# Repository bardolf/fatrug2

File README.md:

# FATRUG2

Fully automatic time project ([FAT](https://en.wikipedia.org/wiki/Fully_automatic_time)), based on [FireBeetle 2 ESP32-E IoT Microcontroller](https://www.dfrobot.com/product-2195.html). 

Usage demonstrated on [the videos](https://youtube.com/playlist?list=PLJGLIG7klYTQjR2PzYD64GDgjGLkynPeX).

Measures time between starting and finishing device. 
Basic features:
- ESP32-E IoT Microcontroller is a device brain.
- Ultrasonic distance sensor HC-SR04 with a threshold 60 - 80cm, could be more, didn't test.
- Reliable distance between devices up to 100m (depends on local conditions).
- Minimum measurement time is 100ms (avoiding false start).
- Systematic error 20-50ms, which I'm lazy to compansate.
- Able to run several hours on 2500mAh battery.
- Mountable to tripod via 1/4-20 UNC thread.

## Electronics

Schema and PCB drawn in KiCAD and files are part of the project. Original idea (and PCB) relied on laser sensor VL53L0X, however the measurement is too bad in noisy environment (sunny day). It was redesign to use ultrasonic sensor HC-SR04 instead. The ultrasonic sensor needs and TM1637 4-Digit LED need 5V (better results with 5V), step up to 5V was added. It is not yet reflected on PCB (maybe future updates), just connected with dupont wires.

Peripherials are following. 
- MCU

- ~~laser distance sensor - GY-VL53L0X I2, connected via connector labeled _laser_ (SDA, SCL, 3.3V, GND)~~

TODO: ultrasonic sensor

- TM1637 4-Digit LED 0.56" 0.56inch 7 Segments Display, connected via connector labeled _7seg_. Beware: more common display is the one with colon wired and dots unwired. Choose based on your preferences.

- RGB LED NeoPixel WS2812 8mm, connected via connector labeled _RGB LED_

- button (reset), connected to ground and PIN D2 (25) 

- LiPol Batterry 104050 2500mAh 3.7V JST-PH 2.0

- switch ([aliexpress](https://www.aliexpress.com/item/1005003268288232.html?spm=a2g0o.order_detail.0.0.5ad3f19ccqQfnJ))

- 2x resistor 20k - for battery capacity measurement on PIN A0 (36)

- some JST-PH connectors, DUPONT connectors

If you make your own BOM don't forget to [multiply it by two](https://youtube.com/clip/UgkxrPXdP5GEu_9O2kQU0yOqQVvTavGrz9Ro) - you need 2 boxes.

TODO: antennas

### PCB

## Box

## State Diagram 

## Photos

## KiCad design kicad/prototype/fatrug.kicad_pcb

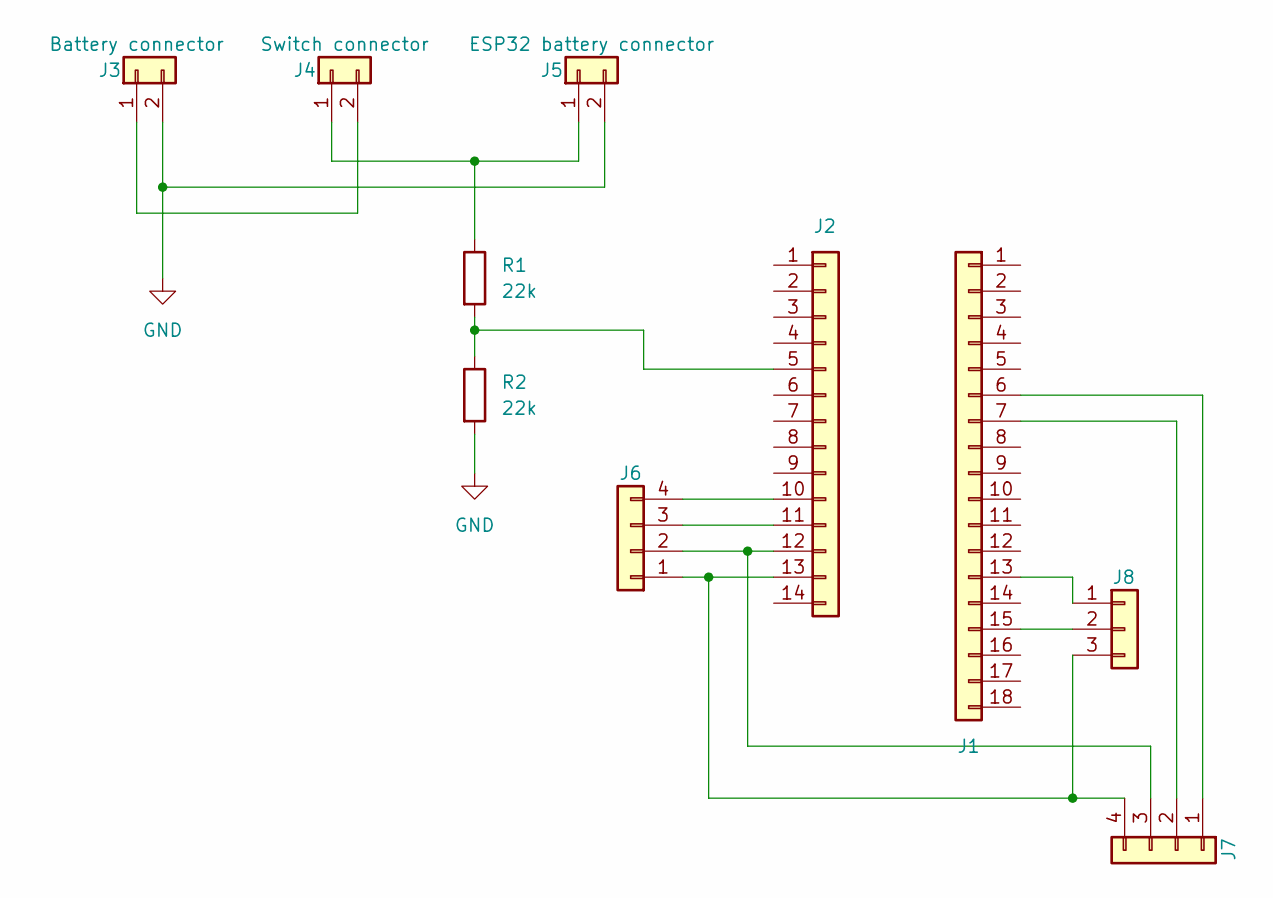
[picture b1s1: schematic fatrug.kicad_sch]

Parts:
J1: Conn_01x18; PinSocket_1x18_P2.54mm_Vertical
J2: Conn_01x14; PinSocket_1x14_P2.54mm_Vertical
J3, J4, J5: Conn_01x02; JST_XH_B2B-XH-AM_1x02_P2.50mm_Vertical
J6, J7: Conn_01x04; PinHeader_1x04_P2.54mm_Vertical
J8: Conn_01x03; PinHeader_1x03_P2.54mm_Vertical
R1, R2: 22k; R_Axial_DIN0204_L3.6mm_D1.6mm_P7.62mm_Horizontal

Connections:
GND: J3.2, J5.2, R2.2
unnamed: J1.6, J7.1
unnamed: J1.7, J7.2
unnamed: J1.13, J8.1
unnamed: J1.15, J8.2
unnamed: J2.10, J6.4
unnamed: J2.11, J6.3
unnamed: J2.12, J6.2, J7.3
unnamed: J2.13, J6.1, J7.4, J8.3
unnamed: J3.1, J4.2
unnamed: J4.1, J5.1, R1.1
unnamed: J2.5, R1.2, R2.1

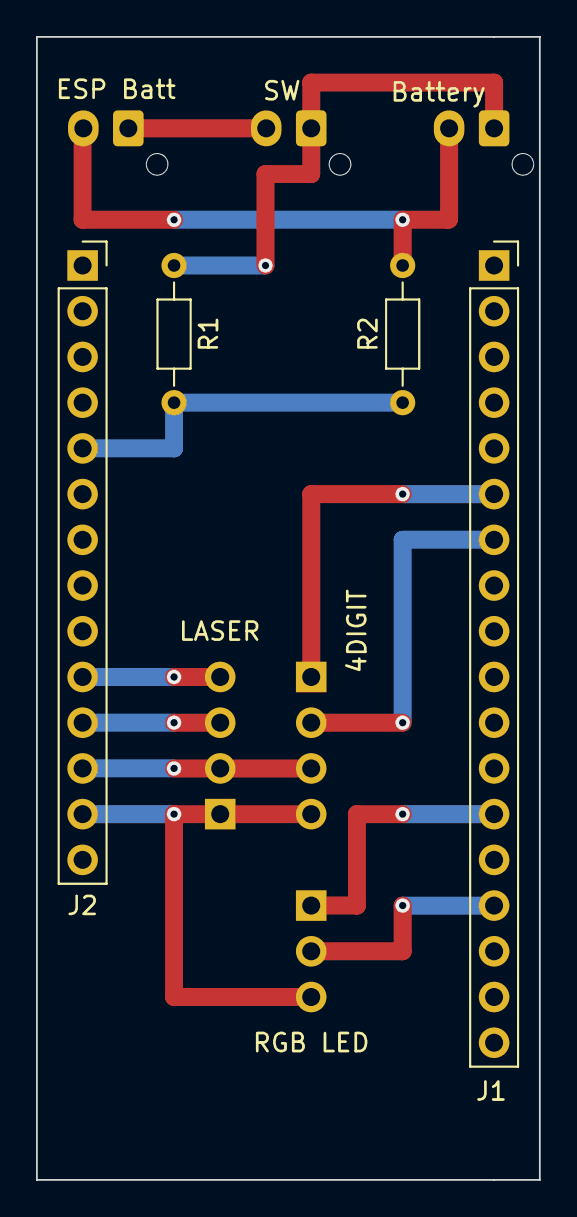
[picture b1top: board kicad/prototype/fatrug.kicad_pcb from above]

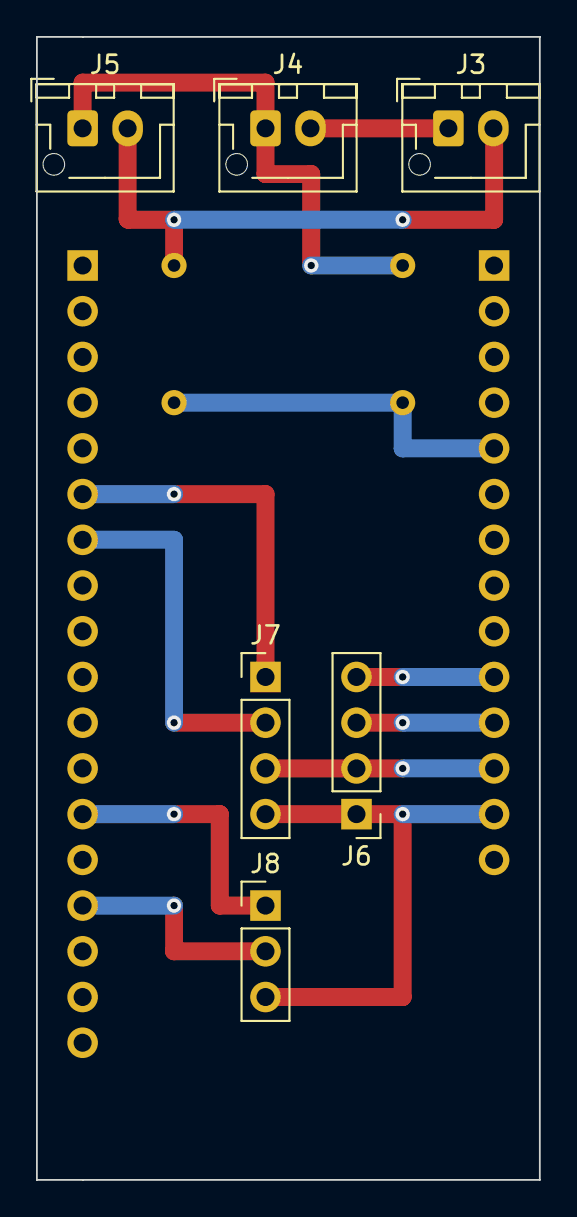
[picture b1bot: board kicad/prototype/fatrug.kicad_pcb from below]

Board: 2 copper layers, 27.9 x 63.5 mm, 10 parts (6 on the bottom side), 12 nets.

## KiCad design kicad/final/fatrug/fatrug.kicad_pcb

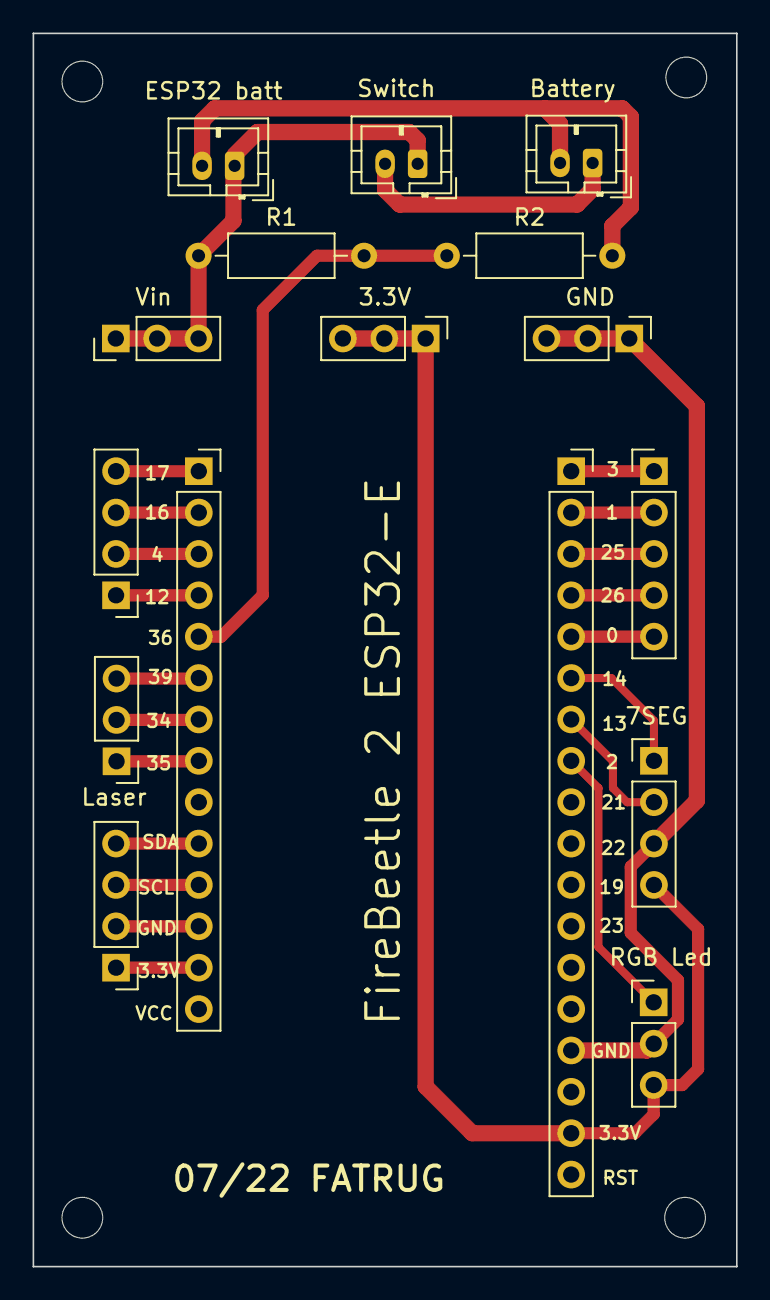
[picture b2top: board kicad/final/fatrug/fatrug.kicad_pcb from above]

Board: 2 copper layers, 43.2 x 75.7 mm, 20 parts (0 on the bottom side), 25 nets.

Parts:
H1, H2, H3, H4: MountingHole; MountingHole_2.5mm
J1, J2, J3: Conn_01x02; JST_PH_B2B-PH-K_1x02_P2.00mm_Vertical
J4, J8, J9: Conn_01x04; PinHeader_1x04_P2.54mm_Vertical
J5: Conn_01x14; PinSocket_1x14_P2.54mm_Vertical
J6: Conn_01x18; PinSocket_1x18_P2.54mm_Vertical
J7, J10, J12, J13, J14: Conn_01x03; PinHeader_1x03_P2.54mm_Vertical
J11: Conn_01x05; PinHeader_1x05_P2.54mm_Vertical
R1, R2: 22k; R_Axial_DIN0207_L6.3mm_D2.5mm_P10.16mm_Horizontal

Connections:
GND: J1.2, J3.2, R2.2
unnamed: J1.1, J2.2
unnamed: J4.1, J5.13
unnamed: J4.2, J5.12
unnamed: J4.3, J5.11
unnamed: J4.4, J5.10
unnamed: J5.1, J9.4
unnamed: J5.2, J9.3
unnamed: J5.3, J9.2
unnamed: J5.4, J9.1
unnamed: J5.5, R1.2, R2.1
unnamed: J5.6, J14.3
unnamed: J5.7, J14.2
unnamed: J5.8, J14.1
unnamed: J6.6, J8.1
unnamed: J6.7, J8.2
unnamed: J6.8, J7.1
unnamed: J6.17, J7.3, J8.4, J13.1, J13.2, J13.3
unnamed: J2.1, J3.1, J10.1, J10.2, J10.3, R1.1
unnamed: J6.1, J11.1
unnamed: J6.2, J11.2
unnamed: J6.3, J11.3
unnamed: J6.4, J11.4
unnamed: J6.5, J11.5
unnamed: J6.15, J7.2, J8.3, J12.1, J12.2, J12.3

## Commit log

2022-08-07 kicad files
2022-08-11 doc updated
2022-08-11 implementation
2022-08-14 freecad box added
2022-08-14 freecad box
2022-08-21 rgbled introduced
2022-08-21 display introduced
2022-08-21 battery introduced
2022-08-23 comment on battery capacity
2022-08-25 display - show time
2022-08-26 logic implementation
2022-08-26 display - zero time, leading zeroes
2022-08-26 state machine, detector
2022-08-29 box updated
2022-08-29 detector updated
2022-09-04 boxes for ultrasonic sensors
2022-09-05 boxe size increased
2022-09-08 detector implementation
2022-09-08 improved display
2022-09-08 battery percentage
2022-09-13 wifi lower rate
